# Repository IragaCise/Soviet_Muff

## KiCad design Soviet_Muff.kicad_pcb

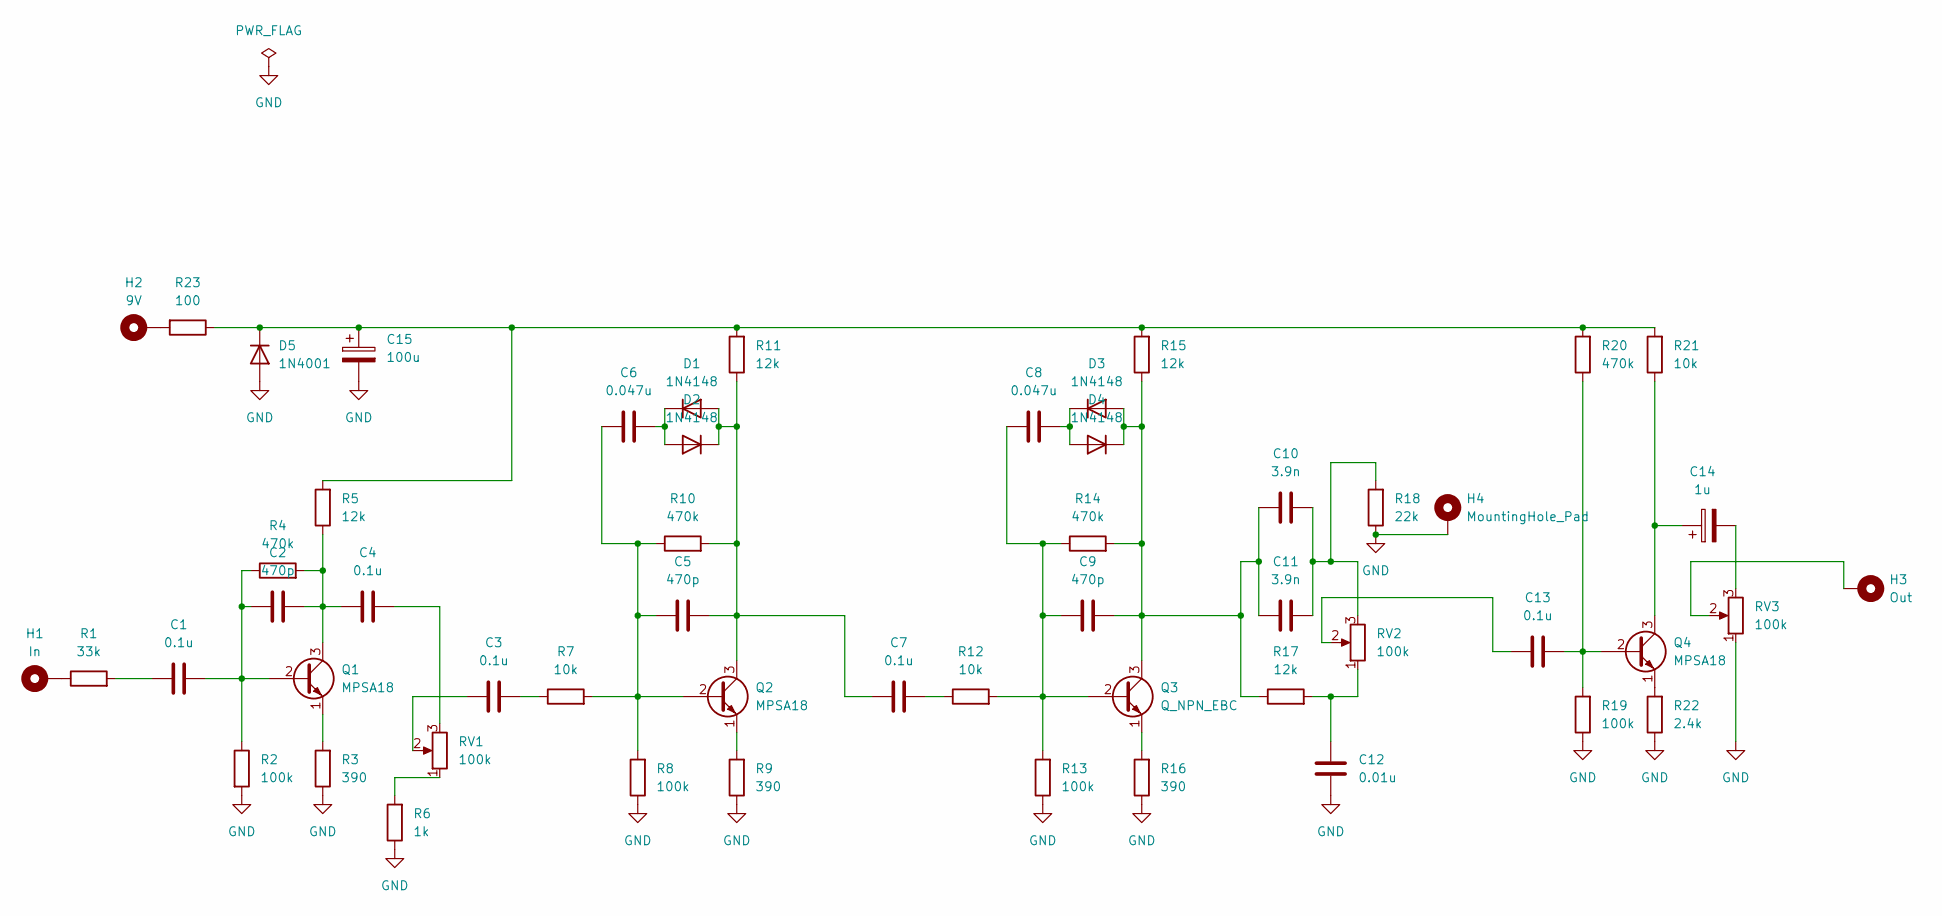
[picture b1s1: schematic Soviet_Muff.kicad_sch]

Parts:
C1, C3, C4, C7, C13: 0.1u; C_Rect_L7.0mm_W2.5mm_P5.00mm
C2, C5, C9: 470p; C_Rect_L7.0mm_W2.5mm_P5.00mm
C6, C8: 0.047u; C_Rect_L7.0mm_W4.0mm_P5.00mm
C10, C11: 3.9n; C_Rect_L6.0mm_W3.0mm_P3.50mm_MKS02_FKP02
C12: 0.01u; C_Rect_L6.5mm_W3.5mm_P3.50mm_MKS02_FKP02
C14: 1u; CP_Radial_D5.0mm_P2.00mm
C15: 100u; CP_Radial_D10.0mm_P5.00mm
D1, D2, D3, D4: 1N4148; D_DO-35_SOD27_P7.62mm_Horizontal
D5: 1N4001; D_DO-41_SOD81_P7.62mm_Horizontal
H1: In; Pad
H2: 9V; Pad
H3: Out; Pad
H4: MountingHole_Pad; Pad
Q1, Q2, Q4: MPSA18; TO-92
Q3: Q_NPN_EBC; TO-92
R1: 33k; R_Axial_DIN0207_L6.3mm_D2.5mm_P7.62mm_Horizontal
R2, R8, R13, R19: 100k; R_Axial_DIN0207_L6.3mm_D2.5mm_P7.62mm_Horizontal
R3, R9, R16: 390; R_Axial_DIN0207_L6.3mm_D2.5mm_P7.62mm_Horizontal
R4, R10, R14, R20: 470k; R_Axial_DIN0207_L6.3mm_D2.5mm_P7.62mm_Horizontal
R5, R11, R15, R17: 12k; R_Axial_DIN0207_L6.3mm_D2.5mm_P7.62mm_Horizontal
R6: 1k; R_Axial_DIN0207_L6.3mm_D2.5mm_P7.62mm_Horizontal
R7, R12, R21: 10k; R_Axial_DIN0207_L6.3mm_D2.5mm_P7.62mm_Horizontal
R18: 22k; R_Axial_DIN0207_L6.3mm_D2.5mm_P7.62mm_Horizontal
R22: 2.4k; R_Axial_DIN0207_L6.3mm_D2.5mm_P7.62mm_Horizontal
R23: 100; R_Axial_DIN0207_L6.3mm_D2.5mm_P7.62mm_Horizontal
RV1, RV2, RV3: 100k; Potentionmeter_Pad

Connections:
GND: C12.1, C15.2, D5.2 (A), H4.1, R2.2, R3.1, R6.1, R8.1, R9.1, R13.1, R16.1, R18.1, R19.1, R22.1, RV3.1; also elsewhere on the board
unnamed: C1.2, R1.2
unnamed: C3.1, R7.1
unnamed: C3.2, RV1.2
unnamed: C4.1, RV1.3
unnamed: C7.1, R12.1
unnamed: C10.2, C11.2, R18.2, RV2.3
unnamed: C12.2, R17.2, RV2.1
unnamed: C13.1, RV2.2
unnamed: C14.2, RV3.3
unnamed: C5.2, C7.2, D1.2 (A), D2.1 (K), Q2.3 (C), R10.2, R11.1
unnamed: C6.2, D1.1 (K), D2.2 (A)
unnamed: C9.2, C10.1, C11.1, D3.2 (A), D4.1 (K), Q3.3 (C), R14.2, R15.1, R17.1
unnamed: C8.2, D3.1 (K), D4.2 (A)
unnamed: C15.1, D5.1 (K), R5.2, R11.2, R15.2, R20.2, R21.2, R23.1
unnamed 15: H1.1, R1.1; also elsewhere on the board
unnamed 16: H2.1, R23.2; also elsewhere on the board
unnamed 17: H3.1, RV3.2; also elsewhere on the board
unnamed: C1.1, C2.2, Q1.2 (B), R2.1, R4.1
unnamed: C2.1, C4.2, Q1.3 (C), R4.2, R5.1
unnamed: Q1.1 (E), R3.2
unnamed: C5.1, C6.1, Q2.2 (B), R7.2, R8.2, R10.1
unnamed: Q2.1 (E), R9.2
unnamed: C8.1, C9.1, Q3.2 (B), R12.2, R13.2, R14.1
unnamed: Q3.1 (E), R16.2
unnamed: C13.2, Q4.2 (B), R19.2, R20.1
unnamed: C14.1, Q4.3 (C), R21.1
unnamed: Q4.1 (E), R22.2
unnamed: R6.2, RV1.1

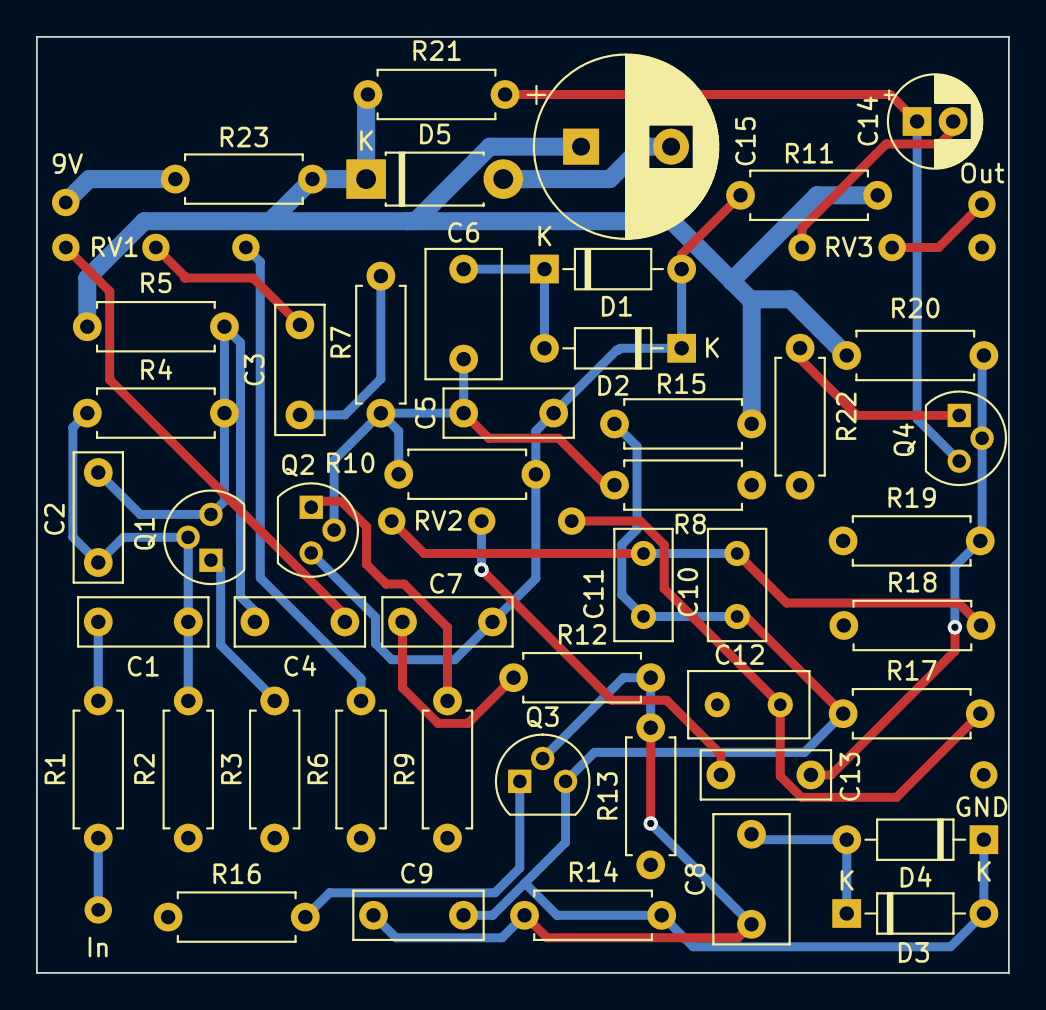
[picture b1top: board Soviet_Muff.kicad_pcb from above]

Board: 2 copper layers, 54.0 x 52.0 mm, 54 parts (0 on the bottom side), 29 nets.

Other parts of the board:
9V: 9V; Pad
GND: MountingHole_Pad; Pad
In: In; Pad
Out: Out; Pad

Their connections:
GND: GND.1; also elsewhere on the board
unnamed 15: In.1; also elsewhere on the board
unnamed 16: 9V.1; also elsewhere on the board
unnamed 17: Out.1; also elsewhere on the board

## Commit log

2025-10-19 v1.0.0
